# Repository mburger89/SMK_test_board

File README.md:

# SMK Test Board

A 3×3 macropad built around the Seeed XIAO ESP32-C6, with a rotary encoder and
per-key RGB. It exists to validate the [SMK](https://github.com/mburger89/SMK)
keyboard firmware and the
[SMK Configurator](https://github.com/mburger89/smk_configurator) editor on real
hardware — small enough to be cheap, complete enough to exercise every subsystem
the full keyboard depends on.

Two of those subsystems have never run against physical hardware at all: the RMT
LED driver and `BatteryMonitor`. This board is where they get their first test.

**The schematic and PCB are generated by a Python script, not drawn by hand.**
`generate_test_board.py` is the source of truth; the files under
`smk_test_board/` are its output and should never be hand-edited.

## Status

Design complete, reviewed, and DRC-clean. **Not yet fabricated.**

Before ordering, `docs/fabrication.md` opens with a STOP gate: two footprints —
`XIAO_ESP32C6_HEADERS` and `EC11_VERTICAL` — were drawn from datasheet
dimensions and have never been checked against real parts. Print the board 1:1
and hold the physical XIAO and EC11 against the paper first. A wrong
castellation pitch or encoder pin spacing is not reworkable; it means a second
fab run.

## What's on it

| | |
|---|---|
| MCU | Seeed XIAO ESP32-C6 on 1×7 female headers |
| Matrix | 3×3, 19.05 mm pitch, Gateron KS-33 hot-swap sockets, SOD-123 diodes |
| Encoder | EC11 vertical; its push-switch **is** matrix position row 0, col 2 |
| RGB | 9 × SK6812MINI-E, reverse-mount, one per key, behind an SN74AHCT1G125 level shifter |
| Power | USB-C on the XIAO, or a single-cell Li-ion via JST **SH** (1.0 mm) with flying leads to the module's underside BAT pads |
| Battery sense | External 1:2 divider (2 × 200 kΩ) into GPIO 0 |
| Board | 2-layer, 65.7 × 91.73 mm, 1.6 mm |

The nine LEDs are reverse-mount and shine *through* milled windows in the board
into each switch's north opening. Those windows are internal `Edge.Cuts`
cutouts, not decoration — a fab house that ignores them produces a board whose
LEDs do nothing.

## Pin map

This is a contract shared by four repositories, and all four must agree:

| Signal | GPIO |
|---|---|
| ROW0–2 | 1, 2, 21 |
| COL0–2 | 22, 23, 16 (`colsAreDriven = 1`) |
| LED data | 20 |
| VBAT sense | 0 (ADC1_CH0) |
| Encoder A/B | 17, 19 |

The four places it appears: `generate_test_board.py`'s `PIN` map, the firmware's
`Main.swift`/`Kconfig.projbuild`, the configurator's
`KeyboardDesign.smkTestBoard`, and this repo's `keymap.json`.

**Encoder rotation is not implemented.** GPIO 17/19 are wired and idle — nothing
decodes quadrature yet. That gets its own design once this board physically
exists. The encoder's *push* works, because it is an ordinary matrix position.

The LED chain is wired **serpentine** (even rows left-to-right, odd rows
right-to-left) to match `ledChainIndex()` in the firmware's
`SMKCore/LEDChainMapping.swift`. This is easy to get wrong and invisible when you
do: on a 3×3, raster and serpentine order agree on rows 0 and 2 and differ only
on row 1. `test_led_chain_order_matches_firmwares_serpentine_mapping` checks all
nine positions for exactly that reason.

## Layout

```
generate_test_board.py     the generator — schematic, PCB, placement, netlist
export_fab.py              gerbers, drill files, and the fab zip
test_test_board.py         netlist, placement, and cross-repo contract tests
test_footprints.py         footprint geometry tests
keymap.json                reference keymap (mo:1 on the encoder press)
smk_test_board/            generated KiCad project — do not hand-edit
smk_test_board.pretty/     local footprint library
docs/fabrication.md        BOM, order spec, DRC triage, pre-order gate
docs/bring-up.md           11-step procedure for a delivered board
docs/superpowers/          design spec and implementation plan
```

## Working on it

```bash
python3 -m venv venv && venv/bin/pip install pytest
venv/bin/python -m pytest          # 28 tests, ~1 min (routes once)
python3 generate_test_board.py     # regenerate the KiCad project
python3 export_fab.py              # gerbers + drill + zip into gerbers/
```

Regeneration is byte-reproducible, UUIDs included — so after any change to the
generator, `git diff` on `smk_test_board/` shows exactly what moved
electrically. If you expected a documentation-only change and the `.kicad_pcb`
moved, that is a real finding, not noise.

Fabrication output lands in `gerbers/` and is gitignored. Generate it fresh at
order time rather than trusting a checked-in copy.

## Bringing one up

`docs/bring-up.md` is an ordered checklist with a blank result field per step.
The order matters: continuity checks happen **before** the XIAO is ever seated,
and the battery flying leads get soldered before anything is powered from a
cell.

Two things reliably waste an afternoon if you don't know them, and both are
called out in that document:

- The firmware's board selection defaults to the *other* board. Flash without
  changing it and you get the wrong pin map, and every matrix test fails
  confusingly.
- Two-Mac bonding needs `CONFIG_BT_NIMBLE_MAX_BONDS=4`. With the default of 1,
  the second Mac evicts the first and the test cannot pass.

## Known and accepted

- The board is **fully routed** — 270 tracks, 83 vias, GND poured on both
  copper layers, 0 unconnected items. It shipped ratsnest-only earlier in
  rev A, and this entry used to say `unconnected_items` was expected and not
  something to "fix"; that is no longer true in either direction. A non-zero
  unconnected count now means a real unrouted connection.
- The outline is **derived, not chosen** — `build_pcb()` sizes it to the
  extent of what it placed, plus a 5 mm margin. It was 76.0 × 113.16 mm
  until the key-field origin and the aux-part placement were tightened to
  make all four margins equal; the same generator run would grow it again if
  a part moved outward. Don't hand-set a board size here — move the parts.
- The GND pours are stored as **outlines only** and filled at the point of
  use. Run DRC with `--refill-zones` and export gerbers with `--check-zones`
  (`export_fab.py` already does) — without them the ground planes are simply
  absent from what you check and what you order.
- `min_copper_edge_clearance` is relaxed to 0.2 mm in the project file, because
  the SK6812 pads sit ~0.233–0.247 mm from their own light windows. That is a
  **relaxed rule, not a passing check.** The basis for proceeding is precedent:
  the sibling `smk_kbd_rp2040` board shipped 59 instances of this exact
  footprint at the same clearance.
- RGB3 will be visibly dimmer than the rest — the EC11's body covers roughly the
  southern half of its light window. Expected, not a fault.
- Li-ion cells are commonly sold with a JST-**PH** (2.0 mm) pigtail, which will
  not mate with this board's **SH** (1.0 mm) connector. Source an SH cell, an
  adapter, or re-terminate.

## Related

- [SMK](https://github.com/mburger89/SMK) — the firmware. Board config lives
  behind `CONFIG_SMK_BOARD_TEST_BOARD`.
- [SMK Configurator](https://github.com/mburger89/smk_configurator) — the
  keymap editor. `KeyboardDesign.smkTestBoard` describes this board's layout,
  and the DEV pane uploads `keymap.json` to it over BLE.

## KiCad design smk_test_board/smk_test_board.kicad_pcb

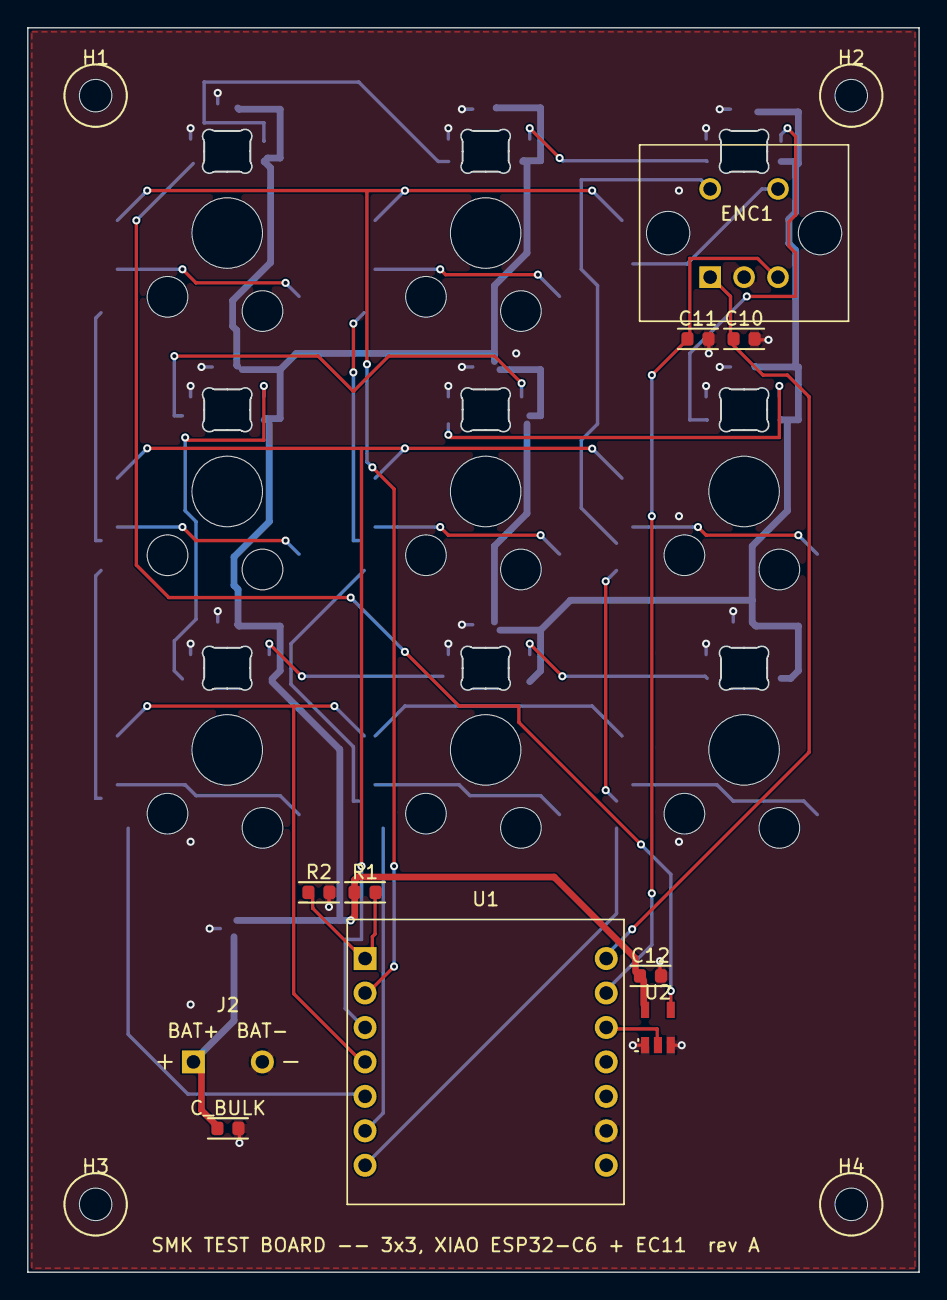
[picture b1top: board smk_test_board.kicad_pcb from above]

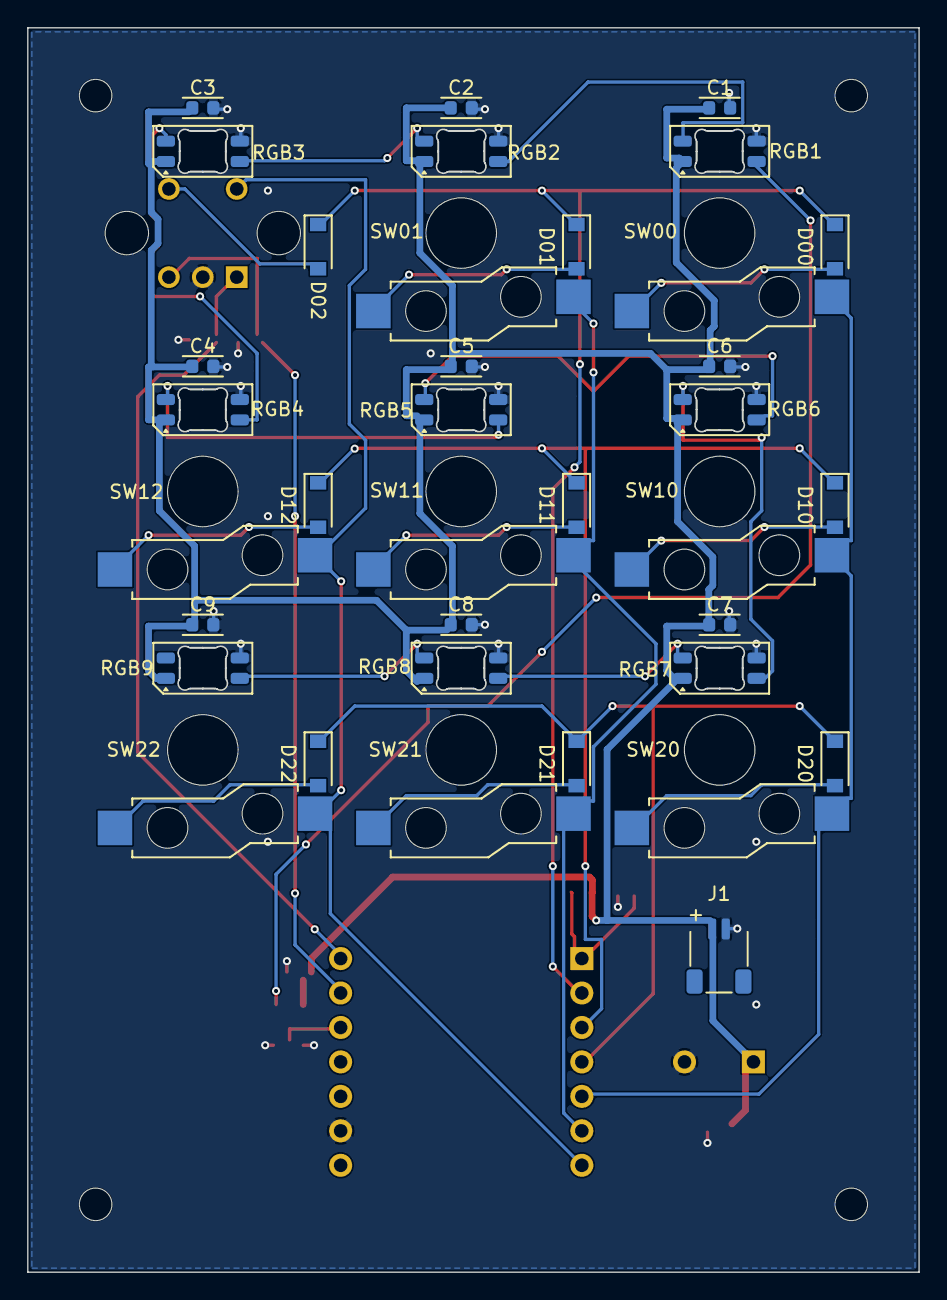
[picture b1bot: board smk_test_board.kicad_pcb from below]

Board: 2 copper layers, 65.7 x 91.7 mm, 50 parts (36 on the bottom side), 30 nets.

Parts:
C1, C2, C3, C4, C5, C6, C7, C8, C9, C10, C11, C12: 100n; RC_0603
C_BULK: 100u; RC_0603
D00, D01, D02, D10, D11, D12, D20, D21, D22: 1N4148W; D_SOD-123_Back
ENC1: EC11 (VERIFY before fab); EC11_VERTICAL
H1, H2, H3, H4: M2; MountingHole_M2
J1: Battery JST-SH; JST_SH_SM02B_2pin_Back
J2: BAT+ / BAT- flying leads; BAT_WIRE_PADS
R1, R2: 200k; RC_0603
RGB1, RGB2, RGB3, RGB4, RGB5, RGB6, RGB7, RGB8, RGB9: SK6812MINI-E; SK6812MINI_E
SW00, SW01, SW10, SW11, SW12, SW20, SW21, SW22: KS-2P02B01-02; SW_Gateron_KS33_HS
U1: XIAO_ESP32C6; XIAO_ESP32C6_HEADERS
U2: SN74AHCT1G125DBVR; SOT-23-5

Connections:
COL0: SW00.1, SW10.1, SW20.1, U1.5
COL1: SW01.1, SW11.1, SW21.1, U1.6
COL2: ENC1.4, SW12.1, SW22.1, U1.7
ENC_A: C10.1, ENC1.1, U1.8
ENC_B: C11.1, ENC1.3, U1.9
GND: C1.2, C2.2, C3.2, C4.2, C5.2, C6.2, C7.2, C8.2, C9.2, C10.2, C11.2, C12.2, C_BULK.2, ENC1.2, J1.2, J2.2, R2.2, RGB1.3, RGB2.3, RGB3.3, RGB4.3, RGB5.3, RGB6.3, RGB7.3, RGB8.3, RGB9.3, U1.13, U2.1, U2.3
LEDD0: U1.10, U2.2
LEDD1: RGB1.4, U2.4
LEDD2: RGB1.2, RGB2.4
LEDD3: RGB2.2, RGB3.4
LEDD4: RGB3.2, RGB4.4
LEDD5: RGB4.2, RGB5.4
LEDD6: RGB5.2, RGB6.4
LEDD7: RGB6.2, RGB7.4
LEDD8: RGB7.2, RGB8.4
LEDD9: RGB8.2, RGB9.4
ROW0: D00.1, D01.1, D02.1, U1.2
ROW1: D10.1, D11.1, D12.1, U1.3
ROW2: D20.1, D21.1, D22.1, U1.4
SW00_N: D00.2, SW00.2
SW01_N: D01.2, SW01.2
SW02_N: D02.2, ENC1.5
SW10_N: D10.2, SW10.2
SW11_N: D11.2, SW11.2
SW12_N: D12.2, SW12.2
SW20_N: D20.2, SW20.2
SW21_N: D21.2, SW21.2
SW22_N: D22.2, SW22.2
VBAT_SENSE: R1.2, R2.1, U1.1
VSYS: C1.1, C2.1, C3.1, C4.1, C5.1, C6.1, C7.1, C8.1, C9.1, C12.1, C_BULK.1, J1.1, J2.1, R1.1, RGB1.1, RGB2.1, RGB3.1, RGB4.1, RGB5.1, RGB6.1, RGB7.1, RGB8.1, RGB9.1, U2.5

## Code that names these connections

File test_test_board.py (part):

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    # These GPIO numbers are the contract with the firmware's board config
    # and the configurator's KeyboardDesign. Changing one without the others
    # produces a board that scans the wrong pins.
    assert tb.PIN["ROW0"] == 1
    assert tb.PIN["ROW1"] == 2
    assert tb.PIN["ROW2"] == 21
    assert tb.PIN["COL0"] == 22
    assert tb.PIN["COL1"] == 23
    assert tb.PIN["COL2"] == 16
    assert tb.PIN["ENC_A"] == 17
    assert tb.PIN["ENC_B"] == 19
    assert tb.PIN["LED_DATA"] == 20
    assert tb.PIN["VBAT_SENSE"] == 0


def test_matrix_is_square_and_matches_led_count():
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

def test_vbat_sense_is_divided_and_wired():
    """PIN["VBAT_SENSE"] existed and drew a schematic port, but build_nets()
    referenced it zero times -- U1 pad 1 was floating while firmware read
    ADC1_CH0 as a battery voltage.

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
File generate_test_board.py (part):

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    # then each DOUT feeds the next DIN. OE# tied to GND permanently
    # enables it; VCC from VSYS (not +3V3) so AHCT's 2.0V input threshold
    # keeps margin against the C6's 3.3V drive across VSYS's whole range.
    add("LEDD0", "U1", "10")                      # GPIO20 -> shifter in
    add("LEDD0", "U2", "A")                        # shifter input
    add("GND", "U2", "OE#")                        # permanently enabled
    add("GND", "U2", "GND")
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    # That is false -- it is the XIAO ESP32-C3/S3 generation that carries an
    # on-module divider; Seeed's own ESP32-C6 battery-monitoring guidance
    # calls for an EXTERNAL 200k/200k pair from BAT to an ADC pin. The spec
    # has been corrected. Before this, PIN["VBAT_SENSE"] existed and drew a
    # schematic port, but build_nets() referenced it zero times: U1 pad 1
    # was a floating input that firmware read as a battery voltage.
    #
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    add("VBAT_SENSE", "R1", "2")
    add("VBAT_SENSE", "R2", "1")
    add("GND", "R2", "2")
    add("VBAT_SENSE", "U1", "1")                  # D0 / GPIO0 / ADC1_CH0

    # U1 pad 12 (+3V3, the XIAO's own regulated logic rail) is left
    # unwired: nothing on this board consumes regulated 3.3V -- the LEDs
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    the two pads carry their own "BAT+"/"BAT-" silk labels, a drawn silk "+"
    sits outboard of pad 1 and a drawn silk "-" outboard of pad 2, and the
    fab-layer body rect is annotated in docs/bring-up.md as the VSYS probe
    point. pinnet keys are footprint pad numbers (1 = BAT+ = VSYS, 2 = BAT- =
    GND)."""
    s = gm.fp_header(_fp("BAT_WIRE_PADS"), ref, "BAT+ / BAT- flying leads",
                      x, y, 0, layer="F.Cu", attr="through_hole",
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    #             pads, so splitting them across U1 would loop that current
    #             the whole way around the module.
    #   C_BULK    LEFT, below J2, i.e. at the power entry. U1 has no VSYS
    #             pin at all (check build_nets(): VSYS's only sources are
    #             J1/J2), so the rail enters the board here -- which is
    #             where a bulk cap belongs, and 25mm nearer than the far
    #             bottom-right corner it used to occupy.
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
